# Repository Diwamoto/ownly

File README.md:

# ownly

ownly is 58 key qwerty custom split keyboard

[buildguide](https://github.com/Diwamoto/ownly/blob/master/docs/buildguide.md "buildguide")

This product released under the GNU GPL.

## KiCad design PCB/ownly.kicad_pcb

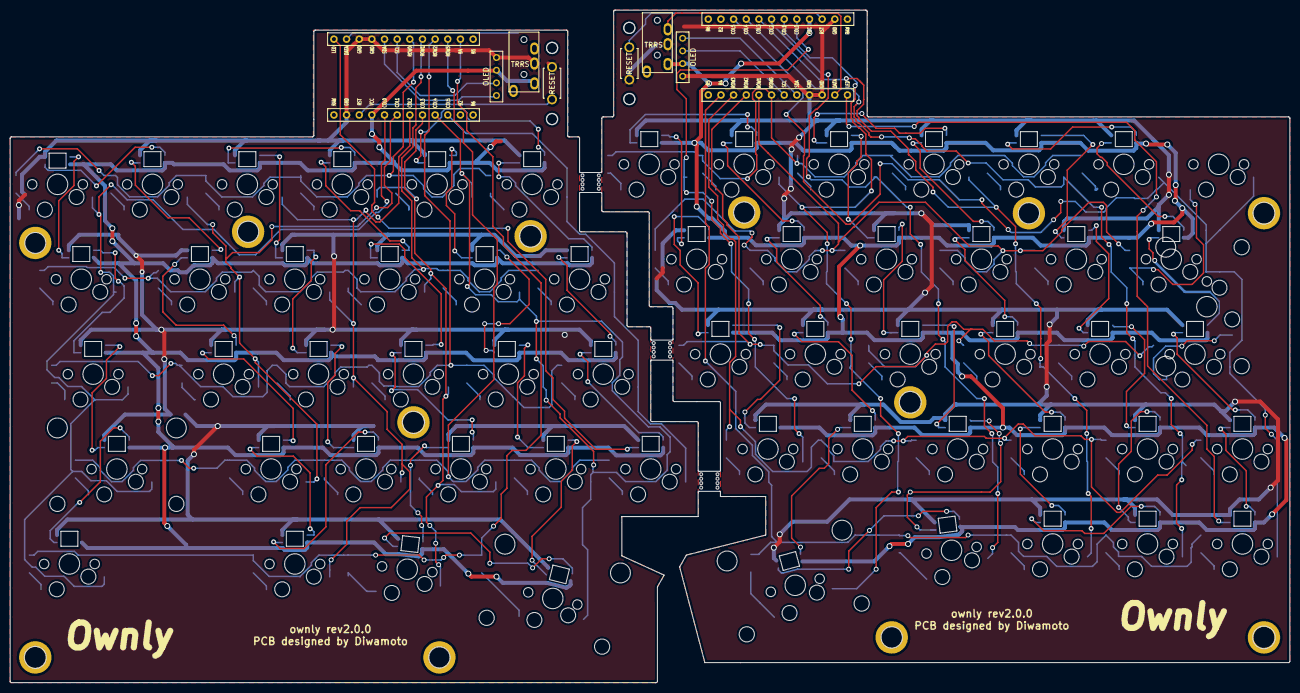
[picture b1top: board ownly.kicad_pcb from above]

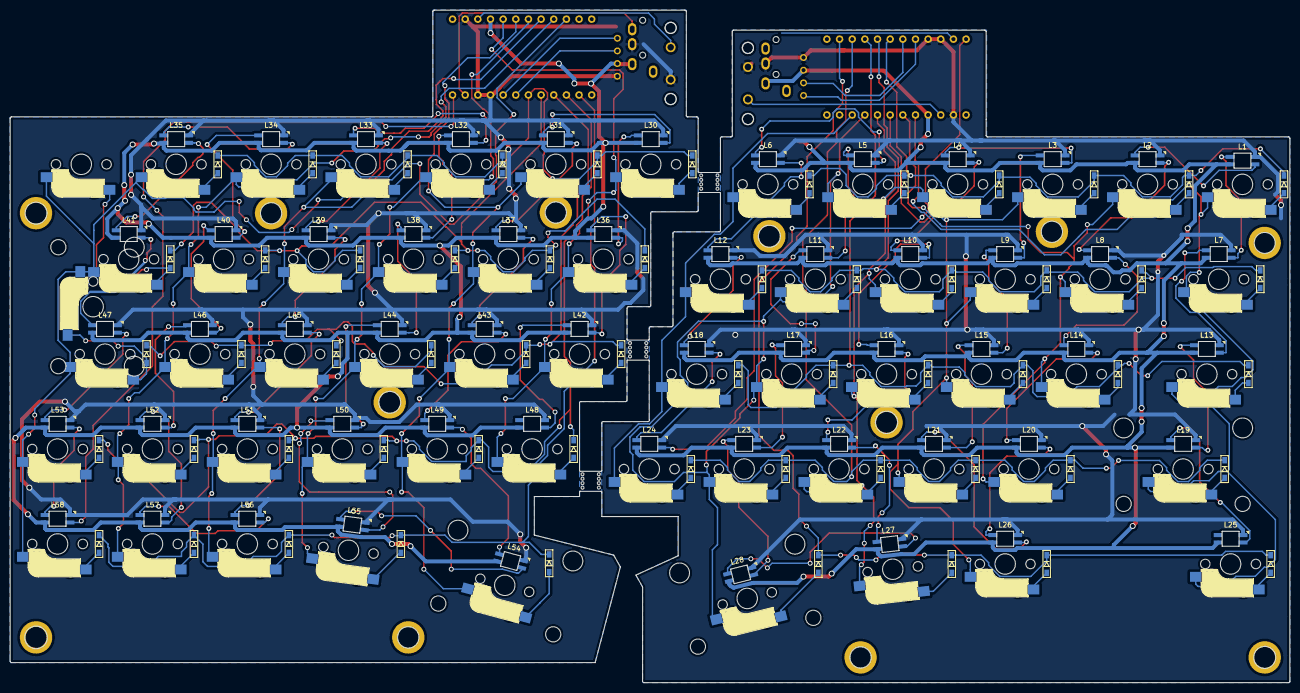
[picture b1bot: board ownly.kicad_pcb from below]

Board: 2 copper layers, 256.8 x 134.9 mm, 197 parts (57 on the bottom side), 146 nets.

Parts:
D1, D2, D3, D4, D5, D6, D7, D8, D9, D10, D11, D12, D13, D14, D15, D16, D17, D18, D19, D20, D21, D22, D23, D24, D25, D26, D27, D28, D30, D31, D32, D33, D34, D35, D36, D37, D38, D39, D40, D41, D42, D43, D44, D45, D46, D47, D48, D49, D50, D51, D52, D53, D54, D55, D56, D57, D58: D; D3_SMD
J1, J5: OLED; OLED_1side
J2, J4: MJ-4PP-9; MJ-4PP-9_1side
L1, L2, L3, L4, L5, L6, L7, L8, L9, L10, L11, L12, L13, L14, L15, L16, L17, L18, L19, L20, L21, L22, L23, L24, L25, L26, L27, L28, L30, L31, L32, L33, L34, L35, L36, L37, L38, L39, L40, L41, L42, L43, L44, L45, L46, L47, L48, L49, L50, L51, L52, L53, L54, L55, L56, L57, L58: YS-SK6812MINI-E
REF3, REF4, REF5, REF6: MountingHole_2.2mm_M2
RSW1, RSW2: SW_PUSH; ResetSW
Ref101: Val1; M2_HOLE
Ref102: Val2; M2_HOLE
Ref104, Ref104#2, Ref104#3, Ref104#4, Ref104#5: Val4; M2_HOLE
Ref107, Ref107#2, Ref107#3, Ref107#4: Val7; M2_HOLE
Ref108: Val8; M2_HOLE
SW1, SW2, SW3, SW4, SW5, SW6, SW8, SW9, SW10, SW11, SW12, SW14, SW15, SW16, SW17, SW18, SW20, SW21, SW22, SW23, SW24, SW27, SW30, SW31, SW32, SW33, SW34, SW35, SW36, SW37, SW38, SW39, SW40, SW41, SW41', SW42, SW43, SW44, SW45, SW46, SW47, SW48, SW49, SW50, SW51, SW52, SW53, SW55, SW56, SW57, SW58: SW_PUSH; CherryMX_Hotswap
SW7: SW_PUSH; CherryMX_Hotswap_1.5u
SW13: SW_PUSH; CherryMX_Hotswap_1.75u
SW19, SW54: SW_PUSH; CherryMX_Hotswap_2.25u
SW25, SW26: SW_PUSH; CherryMX_Hotswap_1.25u
SW28: SW_PUSH; CherryMX_Hotswap_2u
SW47': KEY_SWITCH; CherryMX_Hotswap_iso_enter
U1, U2: ProMicro; ProMicro_v2_1side

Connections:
GND: J1.4, J2.C, J4.C, J5.4, L1.3, L2.3, L3.3, L4.3, L5.3, L6.3, L7.3, L8.3, L9.3, L10.3, L11.3, L12.3, L13.3, L14.3, L15.3, L16.3, L17.3, L18.3, L19.3, L20.3, L21.3, L22.3, L23.3, L24.3, L25.3, L26.3, L27.3, L28.3, L30.3, L31.3, L32.3, L33.3, L34.3, L35.3, L36.3, L37.3, L38.3, L39.3, L40.3, L41.3, L42.3, L43.3, L44.3, L45.3, L46.3, L47.3, L48.3, L49.3, L50.3, L51.3, L52.3, L53.3, L54.3, L55.3, L56.3, L57.3, L58.3, RSW1.2, RSW2.2, U1.3, U1.4, U1.23, U2.3, U2.4, U2.23
LED1: L24.4, U1.1
LED2: L58.4, U2.1
unnamed: D1.2, SW1.2
unnamed: D2.2, SW2.2
unnamed: D3.2, SW3.2
unnamed: D4.2, SW4.2
unnamed: D5.2, SW5.2
unnamed: D6.2, SW6.2
unnamed: D7.2, SW7.2
unnamed: D8.2, SW8.2
unnamed: D9.2, SW9.2
unnamed: D10.2, SW10.2
unnamed: D11.2, SW11.2
unnamed: D12.2, SW12.2
unnamed: D13.2, SW13.2
unnamed: D14.2, SW14.2
unnamed: D15.2, SW15.2
unnamed: D16.2, SW16.2
unnamed: D17.2, SW17.2
unnamed: D18.2, SW18.2
unnamed: D19.2, SW19.2
unnamed: D20.2, SW20.2
unnamed: D21.2, SW21.2
unnamed: D22.2, SW22.2
unnamed: D23.2, SW23.2
unnamed: D24.2, SW24.2
unnamed: D25.2, SW25.2
unnamed: D26.2, SW26.2
unnamed: D27.2, SW27.2
unnamed: D28.2, SW28.2
unnamed: D30.2, SW30.2
unnamed: D31.2, SW31.2
unnamed: D32.2, SW32.2
unnamed: D33.2, SW33.2
unnamed: D34.2, SW34.2
unnamed: D35.2, SW35.2
unnamed: D36.2, SW36.2
unnamed: D37.2, SW37.2
unnamed: D38.2, SW38.2
unnamed: D39.2, SW39.2
unnamed: D40.2, SW40.2
unnamed: D41.2, SW41.2, SW41'.2
unnamed: D42.2, SW42.2
unnamed: D43.2, SW43.2
unnamed: D44.2, SW44.2
unnamed: D45.2, SW45.2
unnamed: D46.2, SW46.2
unnamed: D47.2, SW47.2, SW47'.2
unnamed: D48.2, SW48.2
unnamed: D49.2, SW49.2
unnamed: D50.2, SW50.2
unnamed: D51.2, SW51.2
unnamed: D52.2, SW52.2
unnamed: D53.2, SW53.2
unnamed: D54.2, SW54.2
unnamed: D55.2, SW55.2
unnamed: D56.2, SW56.2
unnamed: D57.2, SW57.2
unnamed: D58.2, SW58.2
unnamed: L1.2, L7.4
unnamed: L1.4, L2.2
unnamed: L2.4, L8.2
unnamed: L3.2, L9.4
unnamed: L3.4, L4.2
unnamed: L5.4, L6.2
unnamed: L4.4, L10.2
unnamed: L10.4, L16.2
unnamed: L11.2, L17.4
unnamed: L5.2, L11.4
unnamed: L6.4, L12.2
unnamed: L12.4, L18.2
unnamed: L13.2, L19.4
unnamed: L7.2, L13.4
unnamed: L8.4, L14.2
unnamed: L14.4, L20.2
unnamed: L15.2, L21.4
unnamed: L9.2, L15.4
unnamed: L16.4, L22.2
unnamed: L17.2, L23.4
unnamed: L18.4, L24.2
unnamed: L19.2, L25.4
unnamed: L20.4, L26.2
unnamed: L21.2, L26.4
unnamed: L22.4, L27.2
unnamed: L23.2, L28.4
unnamed: L27.4, L28.2
unnamed: L30.2, L36.4
unnamed: L30.4, L31.2
unnamed: L31.4, L37.2
unnamed: L32.2, L38.4
unnamed: L32.4, L33.2
unnamed: L33.4, L39.2
unnamed: L34.2, L40.4
unnamed: L34.4, L35.2
unnamed: L35.4, L41.2
unnamed: L36.2, L42.4
unnamed: L37.4, L43.2
unnamed: L38.2, L44.4
unnamed: L39.4, L45.2
unnamed: L40.2, L46.4
unnamed: L41.4, L47.2
unnamed: L42.2, L48.4
unnamed: L43.4, L49.2
unnamed: L44.2, L50.4
unnamed: L45.4, L51.2
unnamed: L46.2, L52.4
unnamed: L47.4, L53.2
unnamed: L49.4, L54.2
unnamed: L50.2, L55.4
unnamed: L51.4, L56.2
unnamed: L52.2, L57.4
unnamed: L53.4, L58.2
unnamed: L54.4, L55.2
unnamed: L56.4, L57.2
SCL1: J5.2, U1.6
SCL2: J1.2, U2.6
SDA1: J5.1, U1.5
SDA2: J1.1, U2.5
VCC: J1.3, J2.D, J4.D, J5.3, L1.1, L2.1, L3.1, L4.1, L5.1, L6.1, L7.1, L8.1, L9.1, L10.1, L11.1, L12.1, L13.1, L14.1, L15.1, L16.1, L17.1, L18.1, L19.1, L20.1, L21.1, L22.1, L23.1, L24.1, L25.1, L26.1, L27.1, L28.1, L30.1, L31.1, L32.1, L33.1, L34.1, L35.1, L36.1, L37.1, L38.1, L39.1, L40.1, L41.1, L42.1, L43.1, L44.1, L45.1, L46.1, L47.1, L48.1, L49.1, L50.1, L51.1, L52.1, L53.1, L54.1, L55.1, L56.1, L57.1, L58.1, U1.21, U2.21
col00: SW30.1, SW36.1, SW42.1, SW48.1, U2.20
col0: SW1.1, SW7.1, SW13.1, SW19.1, SW25.1, U1.20
col01: SW31.1, SW37.1, SW43.1, SW49.1, SW54.1, U2.19
col1: SW2.1, SW8.1, SW14.1, SW20.1, U1.19
col02: SW32.1, SW38.1, SW44.1, SW50.1, SW55.1, U2.18
col2: SW3.1, SW9.1, SW15.1, SW21.1, SW26.1, U1.18
col03: SW33.1, SW39.1, SW45.1, SW51.1, SW56.1, U2.17
col3: SW4.1, SW10.1, SW16.1, SW22.1, SW27.1, U1.17
col04: SW34.1, SW40.1, SW46.1, SW52.1, SW57.1, U2.16
col4: SW5.1, SW11.1, SW17.1, SW23.1, SW28.1, U1.16
col05: SW35.1, SW41.1, SW41'.1, SW47.1, SW47'.1, SW53.1, SW58.1, U2.15
col5: SW6.1, SW12.1, SW18.1, SW24.1, U1.15
data1: J4.B, U1.2
data2: J2.B, U2.2
reset1: RSW1.1, U1.22
reset2: RSW2.1, U2.22
row00: D30.1, D31.1, D32.1, D33.1, D34.1, D35.1, U2.7
row0: D1.1, D2.1, D3.1, D4.1, D5.1, D6.1, U1.7
row01: D36.1, D37.1, D38.1, D39.1, D40.1, D41.1, U2.8
row1: D7.1, D8.1, D9.1, D10.1, D11.1, D12.1, U1.8
row02: D42.1, D43.1, D44.1, D45.1, D46.1, D47.1, U2.9
row2: D13.1, D14.1, D15.1, D16.1, D17.1, D18.1, U1.9
row03: D48.1, D49.1, D50.1, D51.1, D52.1, D53.1, U2.10
row3: D19.1, D20.1, D21.1, D22.1, D23.1, D24.1, U1.10
row04: D54.1, D55.1, D56.1, D57.1, D58.1, U2.11
row4: D25.1, D26.1, D27.1, D28.1, U1.11

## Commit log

2020-08-21 Update MIT License to GPL
    due to using GPL OSS
2020-08-29 dxfファイルとvia用jsoファイルを追加
2020-10-05 製品版をコミット
2020-11-04 ビルドガイドを更新
2020-11-04 画像差し替え
2020-12-26 写真をコミット
2020-12-26 ビルドガイド更新
2020-12-27 ビルドガイドの画像のリンク切れを修正
2020-12-27 リンク切れを調整
2020-12-28 via用のjsonとbmp用のjson公開
2021-01-07 oledのリンクを修正
2021-01-24 画像をコミット
2021-01-24 スタビライザの組み立て方を追加
2021-01-24 説明書を整形
2021-01-24 ビルドガイド更新 rgb_matrixを追加
2021-01-26 ビルドガイド更新ん
2021-02-08 dxfを更新
2021-02-22 デフォルトのファームウェアを追加
2021-02-23 via用のjsonを更新
2021-03-02 配布ファームをRemap対応ファームに変更
2021-03-02 remapに対応している旨を追記
2021-03-04 adding iso enter layout
